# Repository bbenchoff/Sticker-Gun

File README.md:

# The Hackaday Sticker Gun

It's a gun that shoots hackaday stickers. Here's the project: https://hackaday.io/project/5914-the-hackaday-sticker-gun

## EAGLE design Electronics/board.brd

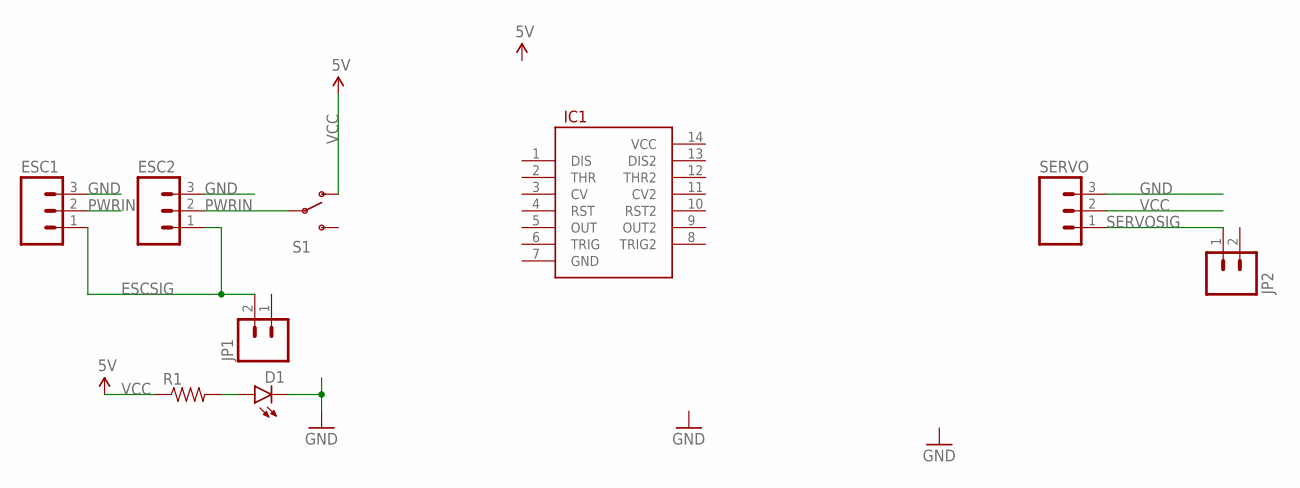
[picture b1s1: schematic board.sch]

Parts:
D1: LED3MM
ESC1, ESC2: M03POGO_PIN_HOLES_ONLY; 1X03_PP_HOLES_ONLY
IC1: 556; DIL14
JP1, JP2: M02PTH; 1X02
R1: RESISTOR0805-RES; 0805
S1: SWITCH-SPDTPTH; SWITCH-SPDT
SERVO: M03POGO_PIN_HOLES_ONLY; 1X03_PP_HOLES_ONLY

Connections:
ESCSIG: ESC1.1, ESC2.1, JP1.2
GND: D1.K (C), ESC1.3, ESC2.3, SERVO.3
unnamed: D1.A, R1.2
PWRIN: ESC1.2, ESC2.2, S1.2
SERVOSIG: JP2.1, SERVO.1
VCC: R1.1, S1.1 (O), SERVO.2

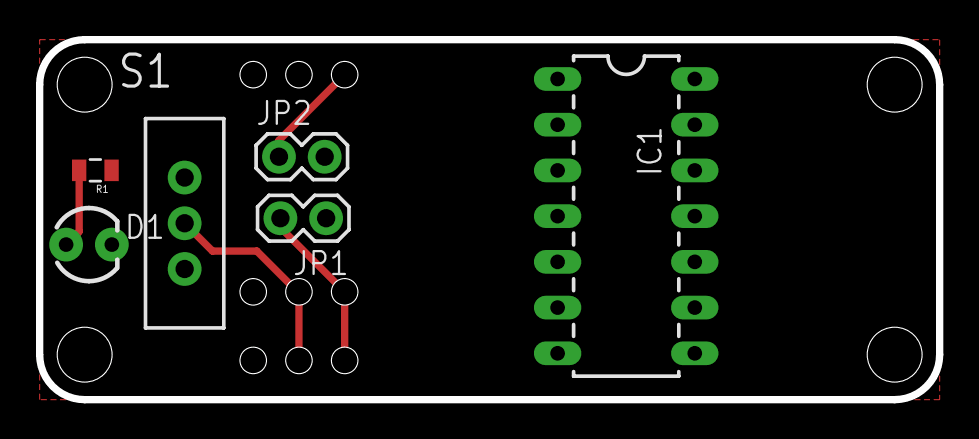
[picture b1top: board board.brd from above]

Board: 2 copper layers, 50.0 x 20.0 mm, 13 parts (0 on the bottom side), 6 nets.

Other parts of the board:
U$5, U$6, U$7, U$8: STAND-OFF-TIGHT

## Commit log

2015-05-21 The Hackaday Sticker Gun
    Uploaded magazine test
2015-05-21 Included the 15k RPM spin wheel
    Woo brushless motors
2015-05-21 Added sticker mule template
2015-06-02 Added Guts
2015-06-02 Added prints
2015-06-02 added magazine
2015-06-02 Fixed guts
2015-06-03 Better guts
2015-06-03 Improved a ton of shit
2015-06-03 More Prints
2015-06-04 added grip
2015-06-05 Begin electronics board
2015-06-08 Added electronics
2015-06-12 Griptop
2015-06-13 Frame

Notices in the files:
parts and their libraries:
SparkFun-AnalogIC: Licensing:Creative Commons ShareAlike 4.0 International - https://creativecommons.org/licenses/by-sa/4.0
